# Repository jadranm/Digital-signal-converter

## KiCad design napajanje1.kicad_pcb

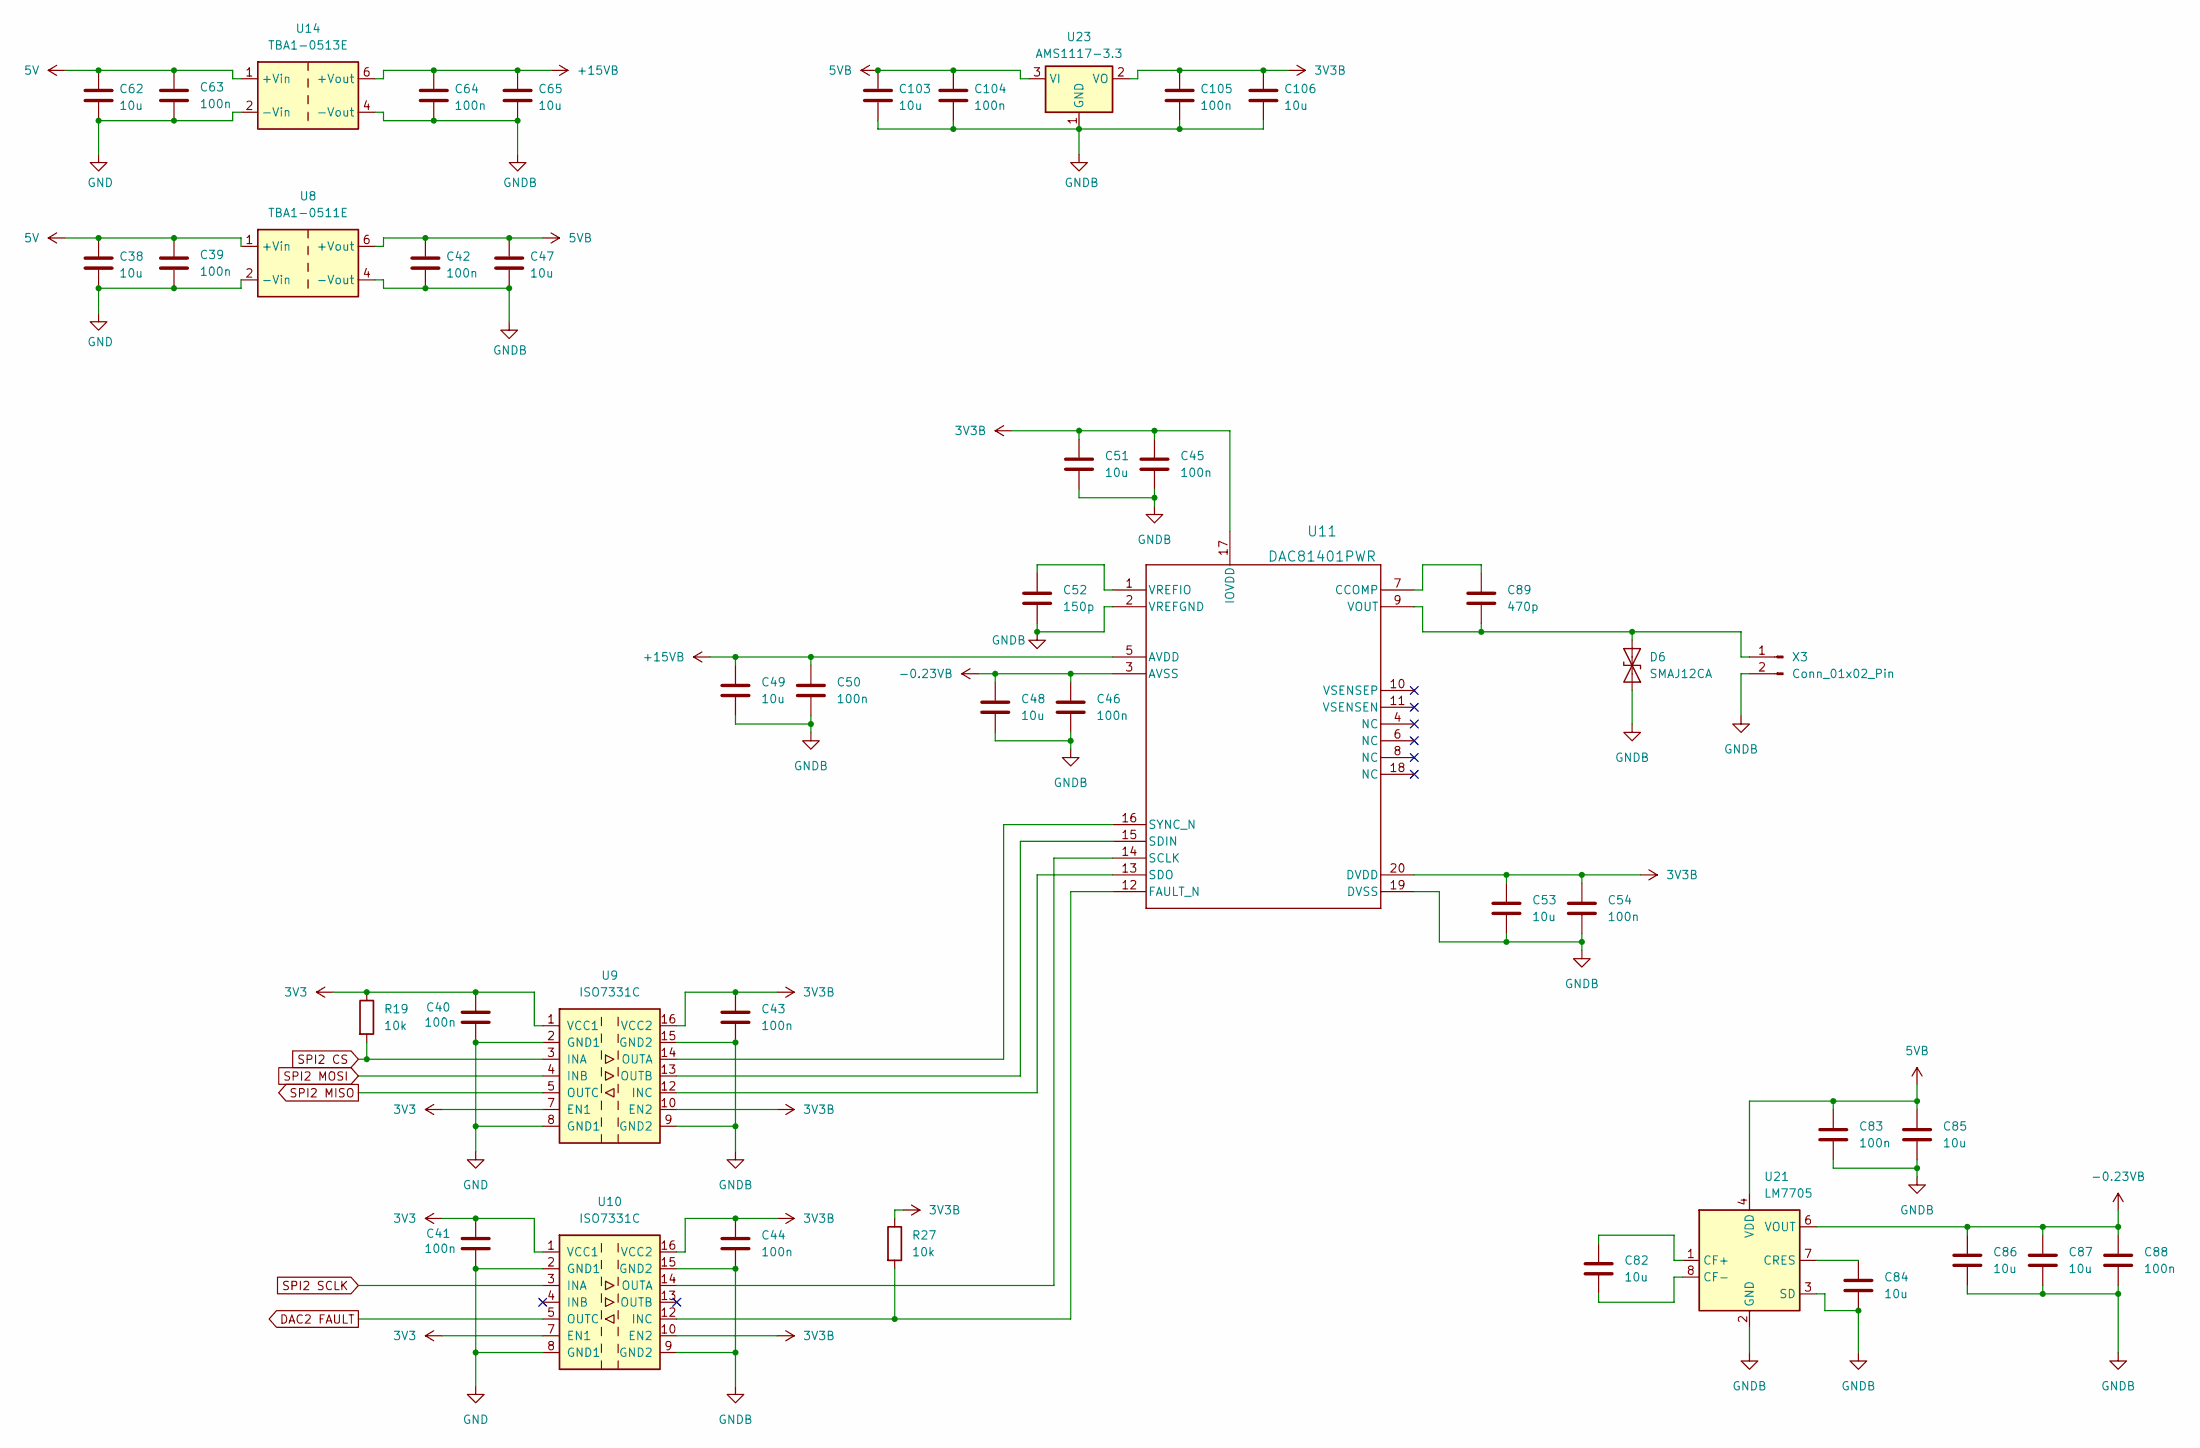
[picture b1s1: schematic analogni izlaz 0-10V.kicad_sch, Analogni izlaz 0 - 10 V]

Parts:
C38, C47, C48, C49, C51, C53, C62, C65, C82, C84, C85, C86, C87, C103, C106: 10u; C_1206_3216Metric_Pad1.33x1.80mm_HandSolder
C39, C40, C41, C42, C43, C44, C45, C46, C50, C54, C63, C64, C83, C88, C104, C105: 100n; C_1206_3216Metric_Pad1.33x1.80mm_HandSolder
C52: 150p; C_1206_3216Metric_Pad1.33x1.80mm_HandSolder
C89: 470p; C_1206_3216Metric_Pad1.33x1.80mm_HandSolder
D6: SMAJ12CA; D_SMA
R19, R27: 10k; R_0805_2012Metric_Pad1.20x1.40mm_HandSolder
U8: TBA1-0511E; Converter_DCDC_TRACO_TBA1-xxxxE_Single_THT
U9, U10: ISO7331C; SOIC-16W_7.5x10.3mm_P1.27mm
U11: DAC81401PWR; Texas_PW0020A_TSSOP-20_4.4x6.5mm_P0.65mm
U14: TBA1-0513E; Converter_DCDC_TRACO_TBA1-xxxxE_Single_THT
U21: LM7705; VSSOP-8_3x3mm_P0.65mm
U23: AMS1117-3.3; SOT-223-3_TabPin2
X3: Conn_01x02_Pin; PhoenixContact_GMSTBA_2,5_2-G-7,62_1x02_P7.62mm_Horizontal

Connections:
3V3: C40.1, C41.1, R19.1, U9.1 (VCC1), U9.7 (EN1), U10.1 (VCC1), U10.7 (EN1); also elsewhere on the board
3V3B: C43.1, C44.1, C45.1, C51.1, C53.1, C54.1, C105.2, C106.2, R27.1, U9.10 (EN2), U9.16 (VCC2), U10.10 (EN2), U10.16 (VCC2), U11.17 (IOVDD), U11.20 (DVDD), U23.2 (VO)
5V: C38.2, C39.2, C62.2, C63.2, U8.1 (+Vin), U14.1 (+Vin); also elsewhere on the board
5VB: C42.2, C47.2, C83.2, C85.2, C103.2, C104.2, U8.6 (+Vout), U21.4 (VDD), U23.3 (VI)
+15VB: C49.1, C50.1, C64.2, C65.2, U11.5 (AVDD), U14.6 (+Vout)
-0.23VB: C46.1, C48.1, C86.2, C87.2, C88.2, U11.3 (AVSS), U21.6 (VOUT)
DAC2 FAULT: U10.5 (OUTC); also elsewhere on the board
GND: C38.1, C39.1, C40.2, C41.2, C62.1, C63.1, U8.2 (-Vin), U9.2 (GND1), U9.8 (GND1), U10.2 (GND1), U10.8 (GND1), U14.2 (-Vin); also elsewhere on the board
GNDB: C42.1, C43.2, C44.2, C45.2, C46.2, C47.1, C48.2, C49.2, C50.2, C51.2, C52.2, C53.2, C54.2, C64.1, C65.1, C83.1, C84.1, C85.1, C86.1, C87.1, C88.1, C103.1, C104.1, C105.1, C106.1, D6.1 (A1), U8.4 (-Vout), U9.9 (GND2), U9.15 (GND2), U10.9 (GND2), U10.15 (GND2), U11.2 (VREFGND), U11.19 (DVSS), U14.4 (-Vout), U21.2 (GND), U21.3 (SD), U21.5 (GND), U23.1 (GND), X3.2
unnamed: C89.2, D6.2 (A2), U11.9 (VOUT), X3.1
unnamed: R27.2, U10.12 (INC), U11.12 (FAULT_N)
unnamed: U10.14 (OUTA), U11.14 (SCLK)
unnamed: C89.1, U11.7 (CCOMP)
unnamed: U9.13 (OUTB), U11.15 (SDIN)
unnamed: U9.12 (INC), U11.13 (SDO)
unnamed: U9.14 (OUTA), U11.16 (SYNC_N)
unnamed: C52.1, U11.1 (VREFIO)
unnamed: C82.2, U21.1 (CF+)
unnamed: C82.1, U21.8 (CF-)
unnamed: C84.2, U21.7 (CRES)
SPI2 CS: R19.2, U9.3 (INA); also elsewhere on the board
SPI2 MISO: U9.5 (OUTC); also elsewhere on the board
SPI2 MOSI: U9.4 (INB); also elsewhere on the board
SPI2 SCLK: U10.3 (INA); also elsewhere on the board

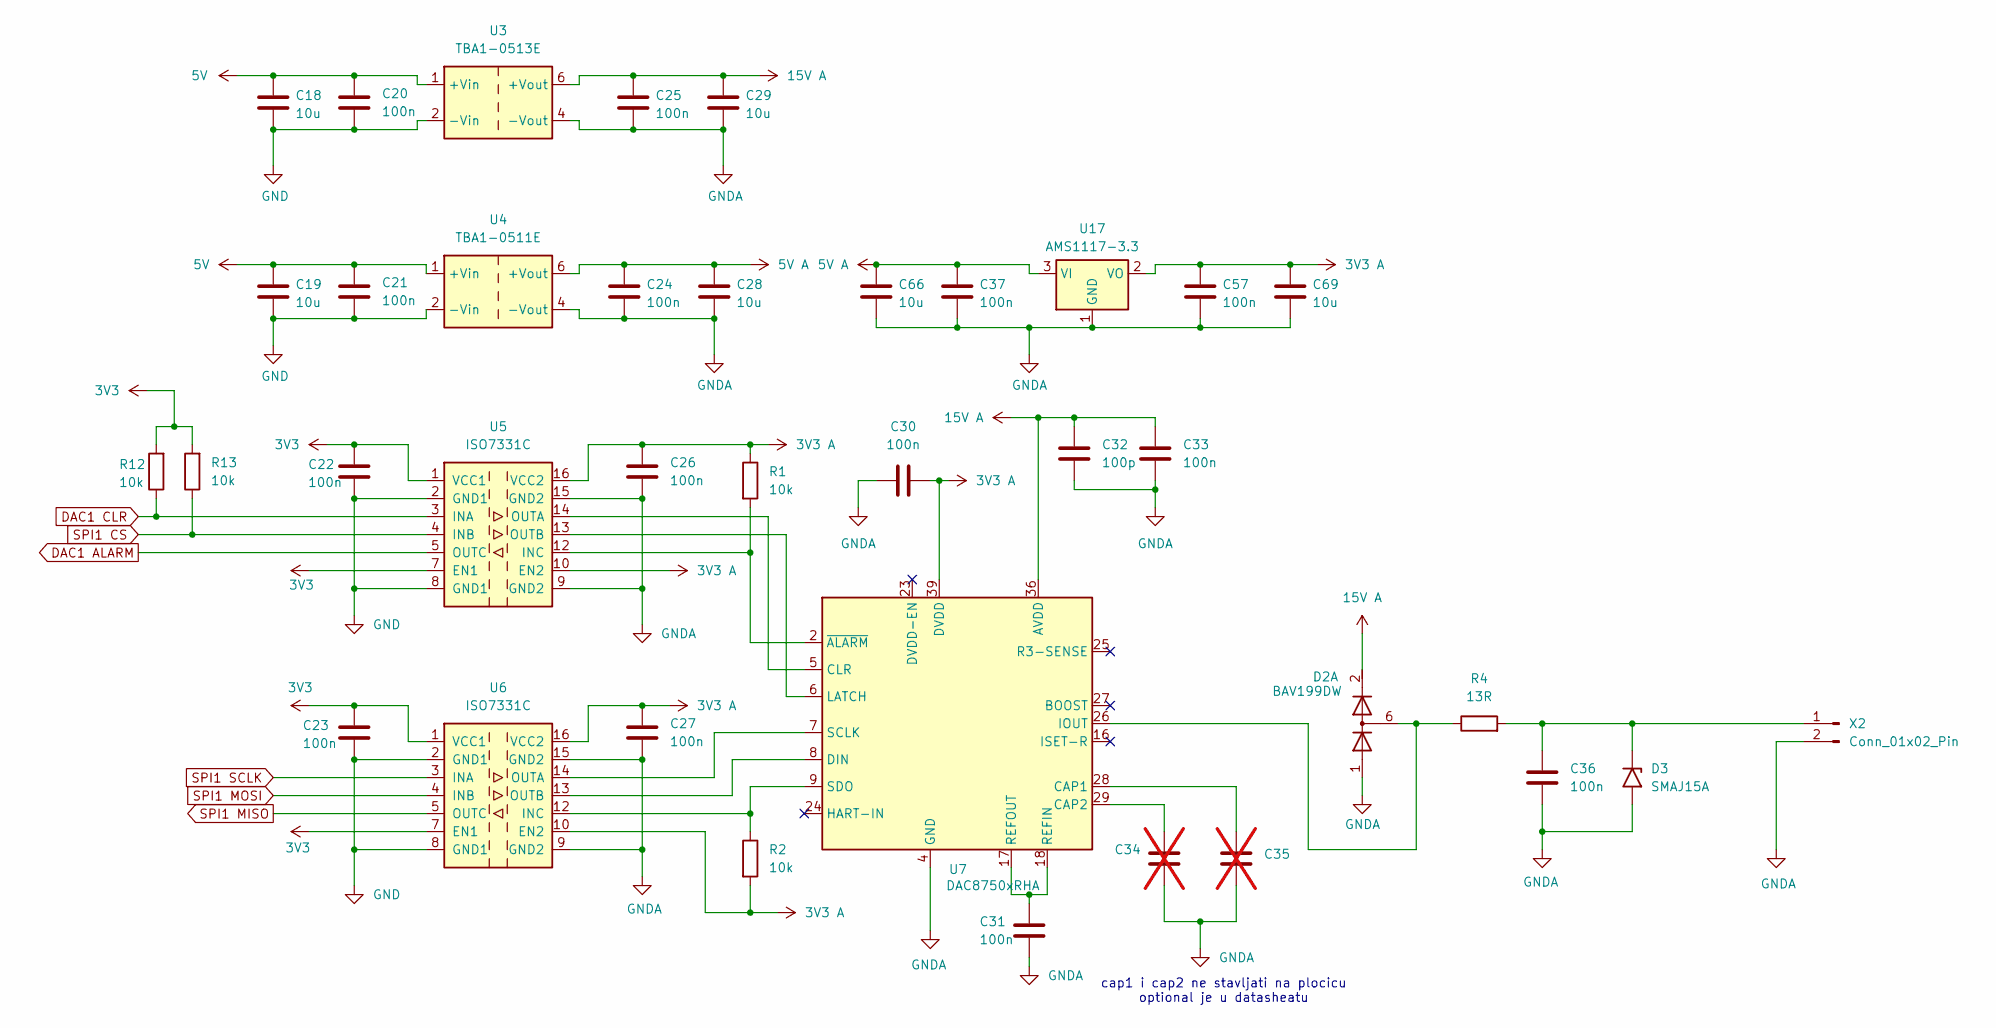
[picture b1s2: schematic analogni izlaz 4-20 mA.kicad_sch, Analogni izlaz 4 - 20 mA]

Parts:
C18, C19, C28, C29, C66, C69: 10u; C_1206_3216Metric_Pad1.33x1.80mm_HandSolder
C20, C21, C22, C23, C24, C25, C26, C27, C30, C31, C33, C36, C37, C57: 100n; C_1206_3216Metric_Pad1.33x1.80mm_HandSolder
C32: 100p; C_1206_3216Metric_Pad1.33x1.80mm_HandSolder
C34, C35: C_1206_3216Metric_Pad1.33x1.80mm_HandSolder; not fitted
D2: BAV199DW; SOT-363_SC-70-6_Handsoldering
D3: SMAJ15A; D_SMA
R1, R2, R12, R13: 10k; R_0805_2012Metric_Pad1.20x1.40mm_HandSolder
R4: 13R; R_0805_2012Metric_Pad1.20x1.40mm_HandSolder
U3: TBA1-0513E; Converter_DCDC_TRACO_TBA1-xxxxE_Single_THT
U4: TBA1-0511E; Converter_DCDC_TRACO_TBA1-xxxxE_Single_THT
U5, U6: ISO7331C; SOIC-16W_7.5x10.3mm_P1.27mm
U7: DAC8750xRHA; Texas_RHA_VQFN-40-1EP_6x6mm_P0.5mm_EP4.6x4.6mm_ThermalVias
U17: AMS1117-3.3; SOT-223-3_TabPin2
X2: Conn_01x02_Pin; PhoenixContact_GMSTBA_2,5_2-G-7,62_1x02_P7.62mm_Horizontal

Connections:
3V3: C22.1, C23.1, R12.2, R13.2, U5.1 (VCC1), U5.7 (EN1), U6.1 (VCC1), U6.7 (EN1); also elsewhere on the board
3V3 A: C26.1, C27.1, C30.2, C57.2, C69.2, R1.1, R2.2, U5.10 (EN2), U5.16 (VCC2), U6.10 (EN2), U6.16 (VCC2), U7.39 (DVDD), U17.2 (VO)
5V: C18.2, C19.2, C20.2, C21.2, U3.1 (+Vin), U4.1 (+Vin); also elsewhere on the board
5V A: C24.2, C28.2, C37.2, C66.2, U4.6 (+Vout), U17.3 (VI)
15V A: C25.2, C29.2, C32.1, C33.1, D2.2 (K2), U3.6 (+Vout), U7.36 (AVDD)
DAC1 ALARM: U5.5 (OUTC); also elsewhere on the board
DAC1 CLR: R12.1, U5.3 (INA); also elsewhere on the board
GND: C18.1, C19.1, C20.1, C21.1, C22.2, C23.2, U3.2 (-Vin), U4.2 (-Vin), U5.2 (GND1), U5.8 (GND1), U6.2 (GND1), U6.8 (GND1); also elsewhere on the board
GNDA: C24.1, C25.1, C26.2, C27.2, C28.1, C29.1, C30.1, C31.2, C32.2, C33.2, C34.2, C35.2, C36.2, C37.1, C57.1, C66.1, C69.1, D2.1 (A1), D3.2 (A2), U3.4 (-Vout), U4.4 (-Vout), U5.9 (GND2), U5.15 (GND2), U6.9 (GND2), U6.15 (GND2), U7.3 (GND), U7.4 (GND), U7.12 (GND), U7.13 (GND), U7.14 (GND), U7.15 (GND), U7.37 (GND), U7.41 (GND), U17.1 (GND), X2.2
unnamed: D2.6 (K3A4), R4.1, U7.26 (IOUT)
unnamed: C36.1, D3.1 (A1), R4.2, X2.1
unnamed: R1.2, U5.12 (INC), U7.2 (~ALARM)
unnamed: U5.14 (OUTA), U7.5 (CLR)
unnamed: U5.13 (OUTB), U7.6 (LATCH)
unnamed: R2.1, U6.12 (INC), U7.9 (SDO)
unnamed: U6.14 (OUTA), U7.7 (SCLK)
unnamed: U6.13 (OUTB), U7.8 (DIN)
unnamed: C35.1, U7.28 (CAP1)
unnamed: C34.1, U7.29 (CAP2)
unnamed: C31.1, U7.17 (REFOUT), U7.18 (REFIN)
SPI1 CS: R13.1, U5.4 (INB); also elsewhere on the board
SPI1 MISO: U6.5 (OUTC); also elsewhere on the board
SPI1 MOSI: U6.4 (INB); also elsewhere on the board
SPI1 SCLK: U6.3 (INA); also elsewhere on the board

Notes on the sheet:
cap1 i cap2 ne stavljati na plocicu optional je u datasheatu

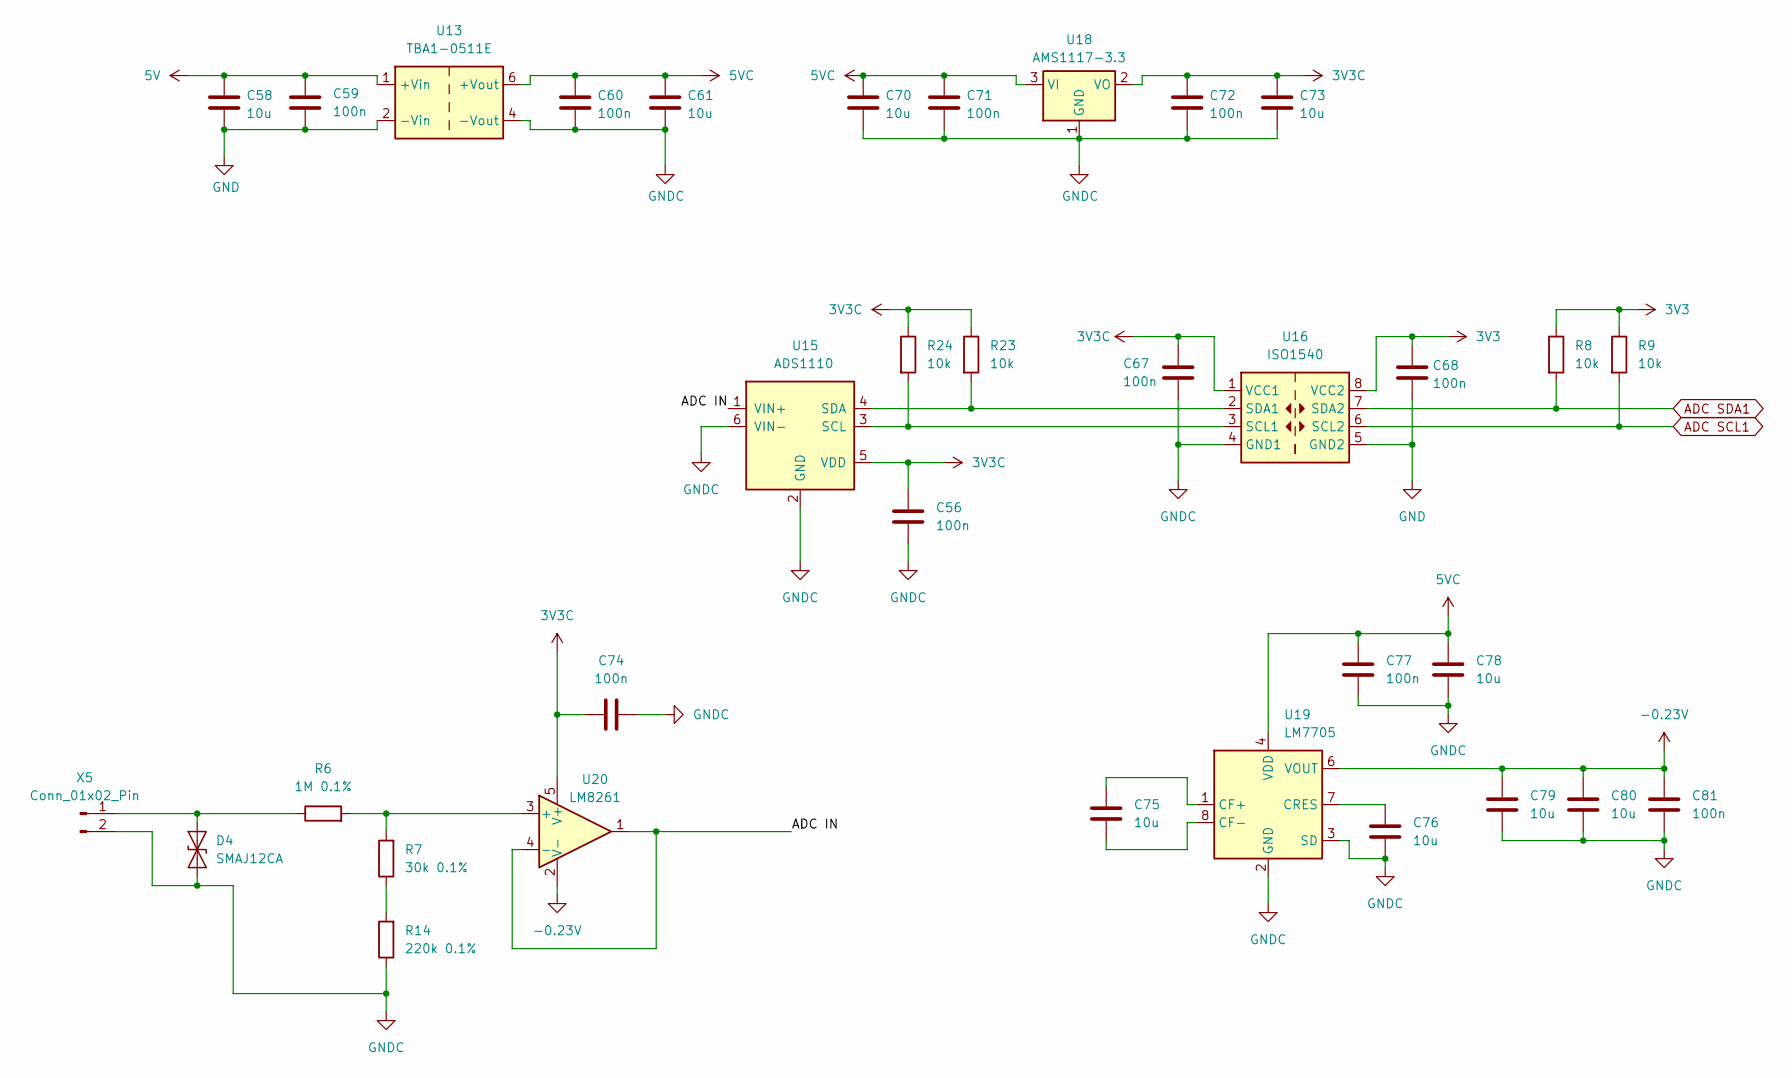
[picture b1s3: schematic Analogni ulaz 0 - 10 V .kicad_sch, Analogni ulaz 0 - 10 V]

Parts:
C56, C59, C60, C67, C68, C71, C72, C74, C77, C81: 100n; C_1206_3216Metric_Pad1.33x1.80mm_HandSolder
C58, C61, C70, C73, C75, C76, C78, C79, C80: 10u; C_1206_3216Metric_Pad1.33x1.80mm_HandSolder
D4: SMAJ12CA; D_SMA
R6: 1M 0.1%; R_0805_2012Metric_Pad1.20x1.40mm_HandSolder
R7: 30k 0.1%; R_0805_2012Metric_Pad1.20x1.40mm_HandSolder
R8, R9, R23, R24: 10k; R_0805_2012Metric_Pad1.20x1.40mm_HandSolder
R14: 220k 0.1%; R_0805_2012Metric_Pad1.20x1.40mm_HandSolder
U13: TBA1-0511E; Converter_DCDC_TRACO_TBA1-xxxxE_Single_THT
U15: ADS1110; SOT-23-6
U16: ISO1540; SOIC-8_3.9x4.9mm_P1.27mm
U18: AMS1117-3.3; SOT-223-3_TabPin2
U19: LM7705; VSSOP-8_3x3mm_P0.65mm
U20: LM8261; SOT-23-5
X5: Conn_01x02_Pin; PhoenixContact_GMSTBA_2,5_2-G-7,62_1x02_P7.62mm_Horizontal

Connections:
3V3: C68.1, R8.1, R9.1, U16.8 (VCC2); also elsewhere on the board
3V3C: C56.1, C67.1, C72.2, C73.2, C74.1, R23.1, R24.1, U15.5 (VDD), U16.1 (VCC1), U18.2 (VO), U20.5 (V+)
5V: C58.2, C59.2, U13.1 (+Vin); also elsewhere on the board
5VC: C60.2, C61.2, C70.2, C71.2, C77.2, C78.2, U13.6 (+Vout), U18.3 (VI), U19.4 (VDD)
-0.23V: C79.2, C80.2, C81.2, U19.6 (VOUT), U20.2 (V-)
/Analogni ulaz 0 - 10 V/ADC IN: U15.1 (VIN+), U20.1, U20.4 (-)
ADC SCL1: R9.2, U16.6 (SCL2); also elsewhere on the board
ADC SDA1: R8.2, U16.7 (SDA2); also elsewhere on the board
GND: C58.1, C59.1, C68.2, U13.2 (-Vin), U16.5 (GND2); also elsewhere on the board
GNDC: C56.2, C60.1, C61.1, C67.2, C70.1, C71.1, C72.1, C73.1, C74.2, C76.1, C77.1, C78.1, C79.1, C80.1, C81.1, D4.1 (A1), R14.1, U13.4 (-Vout), U15.2 (GND), U15.6 (VIN-), U16.4 (GND1), U18.1 (GND), U19.2 (GND), U19.3 (SD), U19.5 (GND), X5.2
unnamed: D4.2 (A2), R6.1, X5.1
unnamed: R7.1, R14.2
unnamed: R24.2, U15.3 (SCL), U16.3 (SCL1)
unnamed: R23.2, U15.4 (SDA), U16.2 (SDA1)
unnamed: C75.2, U19.1 (CF+)
unnamed: C75.1, U19.8 (CF-)
unnamed: C76.2, U19.7 (CRES)
unnamed: R6.2, R7.2, U20.3 (+)

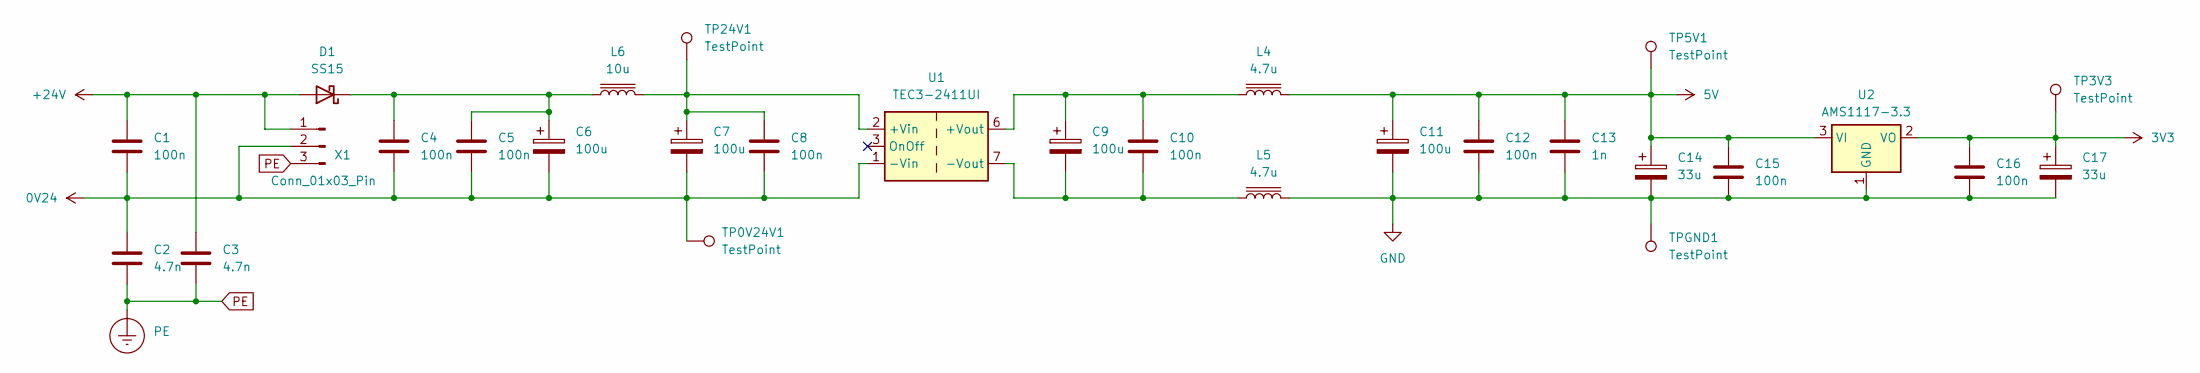
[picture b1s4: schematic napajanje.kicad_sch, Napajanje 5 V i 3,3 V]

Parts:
C1, C4, C5, C8, C10, C12, C15, C16: 100n; C_1206_3216Metric_Pad1.33x1.80mm_HandSolder
C2, C3: 4.7n; C_1206_3216Metric_Pad1.33x1.80mm_HandSolder
C6, C7, C9, C11: 100u; CP_Radial_D6.3mm_P2.50mm
C13: 1n; C_1206_3216Metric_Pad1.33x1.80mm_HandSolder
C14, C17: 33u; CP_Radial_D6.3mm_P2.50mm
D1: SS15; D_2010_5025Metric_Pad1.52x2.65mm_HandSolder
L4, L5: 4.7u; L_1008_2520Metric_Pad1.43x2.20mm_HandSolder
L6: 10u; L_1008_2520Metric_Pad1.43x2.20mm_HandSolder
TP0V24V1, TP3V3, TP5V1, TP24V1: TestPoint; TestPoint_Loop_D1.80mm_Drill1.0mm_Beaded
TPGND1: TestPoint; TestPoint_Loop_D1.80mm_Drill1.0mm_Beaded
U1: TEC3-2411UI; Converter_DCDC_TRACO_TEC3-24xxUI_THT
U2: AMS1117-3.3; SOT-223-3_TabPin2
X1: Conn_01x03_Pin; PhoenixContact_GMSTBA_2,5_3-G-7,62_1x03_P7.62mm_Horizontal

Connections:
0V24: C1.2, C2.1, C4.2, C5.2, C6.2, C7.2, C8.2, TP0V24V1.1, U1.1 (-Vin), X1.2
3V3: C16.1, C17.1, TP3V3.1, U2.2 (VO); also elsewhere on the board
5V: C11.1, C12.1, C13.1, C14.1, C15.1, L4.2, TP5V1.1, U2.3 (VI); also elsewhere on the board
+24V: C1.1, C3.1, D1.2 (A), X1.1
GND: C11.2, C12.2, C13.2, C14.2, C15.2, C16.2, C17.2, L5.2, TPGND1.1, U2.1 (GND); also elsewhere on the board
unnamed: C4.1, C5.1, C6.1, D1.1 (K), L6.1
unnamed: C7.1, C8.1, L6.2, TP24V1.1, U1.2 (+Vin)
unnamed: C9.1, C10.1, L4.1, U1.6 (+Vout)
unnamed: C9.2, C10.2, L5.1, U1.7 (-Vout)
PE: C2.2, C3.2, X1.3

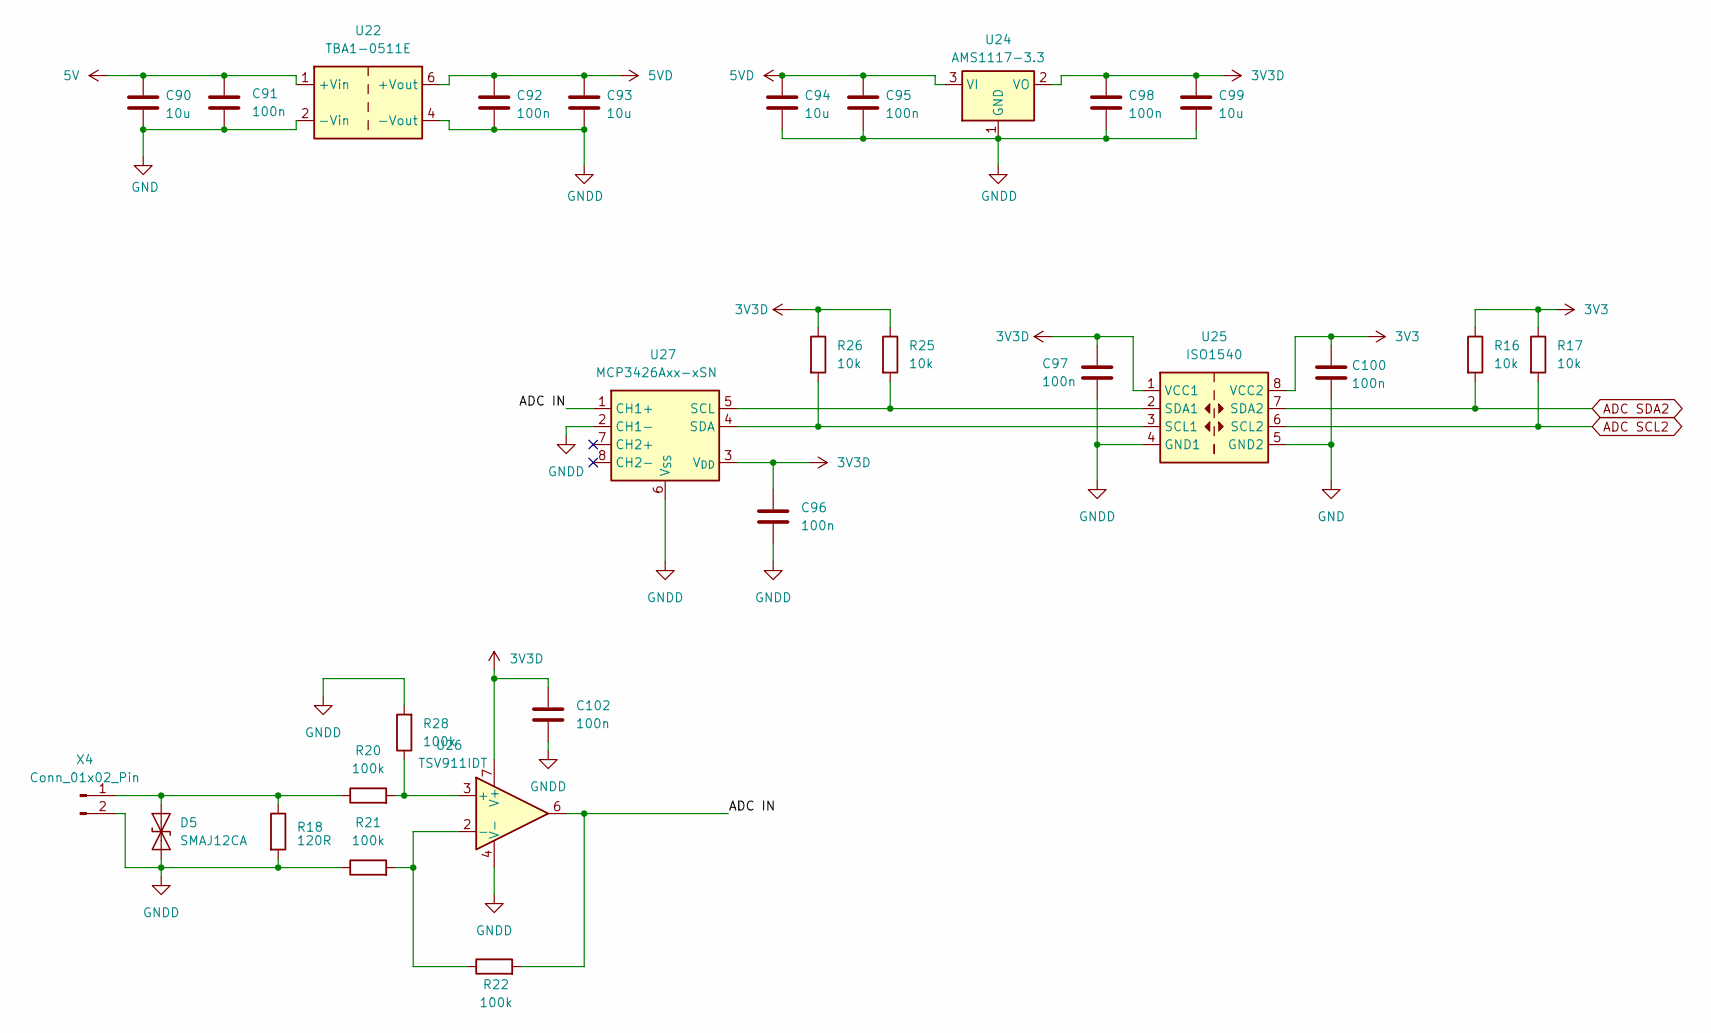
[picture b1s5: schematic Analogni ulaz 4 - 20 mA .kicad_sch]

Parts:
C90, C93, C94, C99: 10u; C_1206_3216Metric_Pad1.33x1.80mm_HandSolder
C91, C92, C95, C96, C97, C98, C100, C102: 100n; C_1206_3216Metric_Pad1.33x1.80mm_HandSolder
D5: SMAJ12CA; D_SMA
R16, R17, R25, R26: 10k; R_0805_2012Metric_Pad1.20x1.40mm_HandSolder
R18: 120R; R_1210_3225Metric
R20, R21, R22, R28: 100k; R_1210_3225Metric
U22: TBA1-0511E; Converter_DCDC_TRACO_TBA1-xxxxE_Single_THT
U24: AMS1117-3.3; SOT-223-3_TabPin2
U25: ISO1540; SOIC-8_3.9x4.9mm_P1.27mm
U26: TSV911IDT; SOIC-8_3.9x4.9mm_P1.27mm
U27: MCP3426Axx-xSN; SOIC-8_3.9x4.9mm_P1.27mm
X4: Conn_01x02_Pin; PhoenixContact_GMSTBA_2,5_2-G-7,62_1x02_P7.62mm_Horizontal

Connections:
3V3: C100.1, R16.1, R17.1, U25.8 (VCC2); also elsewhere on the board
3V3D: C96.1, C97.1, C98.2, C99.2, C102.1, R25.1, R26.1, U24.2 (VO), U25.1 (VCC1), U26.7 (V+), U27.3 (V_{DD})
5V: C90.2, C91.2, U22.1 (+Vin); also elsewhere on the board
5VD: C92.2, C93.2, C94.2, C95.2, U22.6 (+Vout), U24.3 (VI)
/Analogni ulaz 4 - 20 mA/ADC IN: R22.2, U26.6, U27.1 (CH1+)
ADC SCL2: R17.2, U25.6 (SCL2); also elsewhere on the board
ADC SDA2: R16.2, U25.7 (SDA2); also elsewhere on the board
GND: C90.1, C91.1, C100.2, U22.2 (-Vin), U25.5 (GND2); also elsewhere on the board
GNDD: C92.1, C93.1, C94.1, C95.1, C96.2, C97.2, C98.1, C99.1, C102.2, D5.1 (A1), R18.2, R21.1, R28.2, U22.4 (-Vout), U24.1 (GND), U25.4 (GND1), U26.4 (V-), U27.2 (CH1-), U27.6 (V_{SS}), X4.2
unnamed: D5.2 (A2), R18.1, R20.1, X4.1
unnamed: R26.2, U25.3 (SCL1), U27.4 (SDA)
unnamed: R25.2, U25.2 (SDA1), U27.5 (SCL)
unnamed: R20.2, R28.1, U26.3 (+)
unnamed: R21.2, R22.1, U26.2 (-)

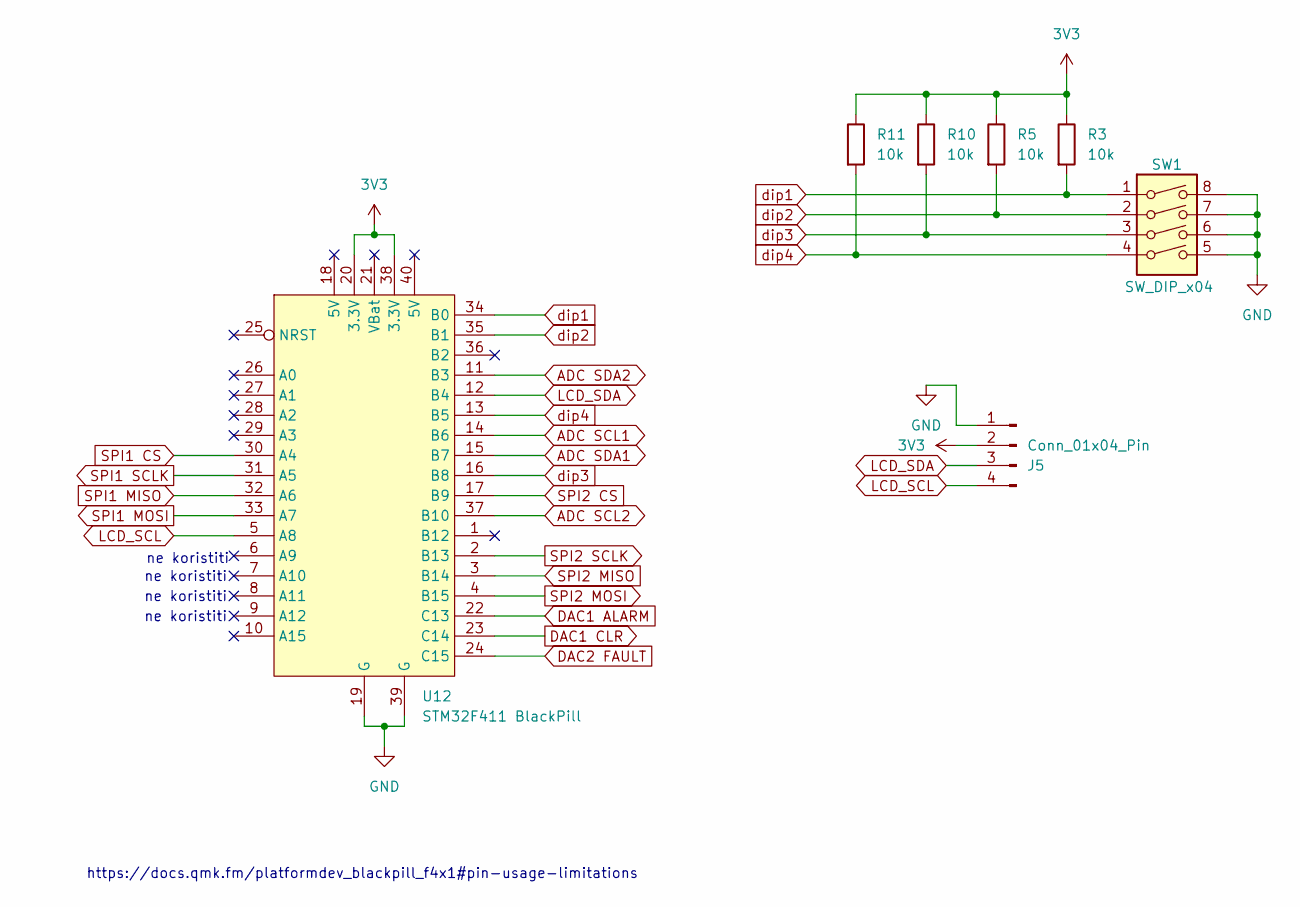
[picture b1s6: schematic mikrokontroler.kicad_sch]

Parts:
J5: Conn_01x04_Pin; PinHeader_1x04_P1.27mm_Vertical
R3, R5, R10, R11: 10k; R_0805_2012Metric_Pad1.20x1.40mm_HandSolder
SW1: SW_DIP_x04; SW_DIP_SPSTx04_Slide_9.78x12.34mm_W7.62mm_P2.54mm
U12: STM32F411 BlackPill; STM32F411_Black_Pill

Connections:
3V3: J5.2, R3.1, R5.1, R10.1, R11.1, U12.20 (3.3V), U12.38 (3.3V); also elsewhere on the board
ADC SCL1: U12.14 (B6); also elsewhere on the board
ADC SCL2: U12.37 (B10); also elsewhere on the board
ADC SDA1: U12.15 (B7); also elsewhere on the board
ADC SDA2: U12.11 (B3); also elsewhere on the board
DAC1 ALARM: U12.22 (C13); also elsewhere on the board
DAC1 CLR: U12.23 (C14); also elsewhere on the board
DAC2 FAULT: U12.24 (C15); also elsewhere on the board
GND: J5.1, SW1.5, SW1.6, SW1.7, SW1.8, U12.19 (G), U12.39 (G); also elsewhere on the board
LCD_SCL: J5.4, U12.5 (A8)
LCD_SDA: J5.3, U12.12 (B4)
SPI1 CS: U12.30 (A4); also elsewhere on the board
SPI1 MISO: U12.32 (A6); also elsewhere on the board
SPI1 MOSI: U12.33 (A7); also elsewhere on the board
SPI1 SCLK: U12.31 (A5); also elsewhere on the board
SPI2 CS: U12.17 (B9); also elsewhere on the board
SPI2 MISO: U12.3 (B14); also elsewhere on the board
SPI2 MOSI: U12.4 (B15); also elsewhere on the board
SPI2 SCLK: U12.2 (B13); also elsewhere on the board
dip1: R3.2, SW1.1, U12.34 (B0)
dip2: R5.2, SW1.2, U12.35 (B1)
dip3: R10.2, SW1.3, U12.16 (B8)
dip4: R11.2, SW1.4, U12.13 (B5)

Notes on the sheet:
https://docs.qmk.fm/platformdev_blackpill_f4x1#pin-usage-limitations
ne koristiti

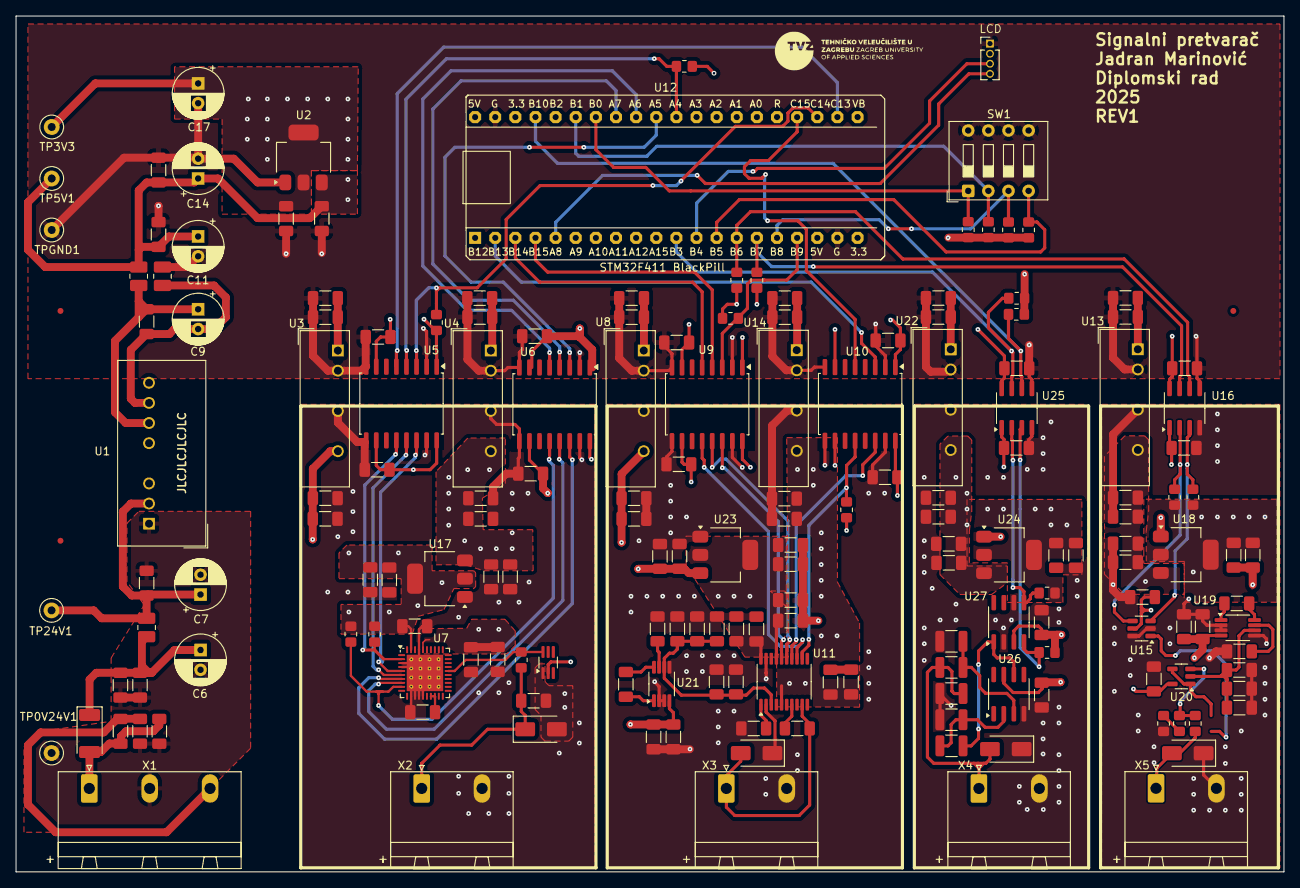
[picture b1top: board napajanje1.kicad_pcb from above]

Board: 4 copper layers, 160.0 x 108.0 mm, 177 parts (0 on the bottom side), 82 nets.
